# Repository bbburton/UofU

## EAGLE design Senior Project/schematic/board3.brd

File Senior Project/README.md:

# senior-project
Documentation and code for the 2022 UofU Senior Project

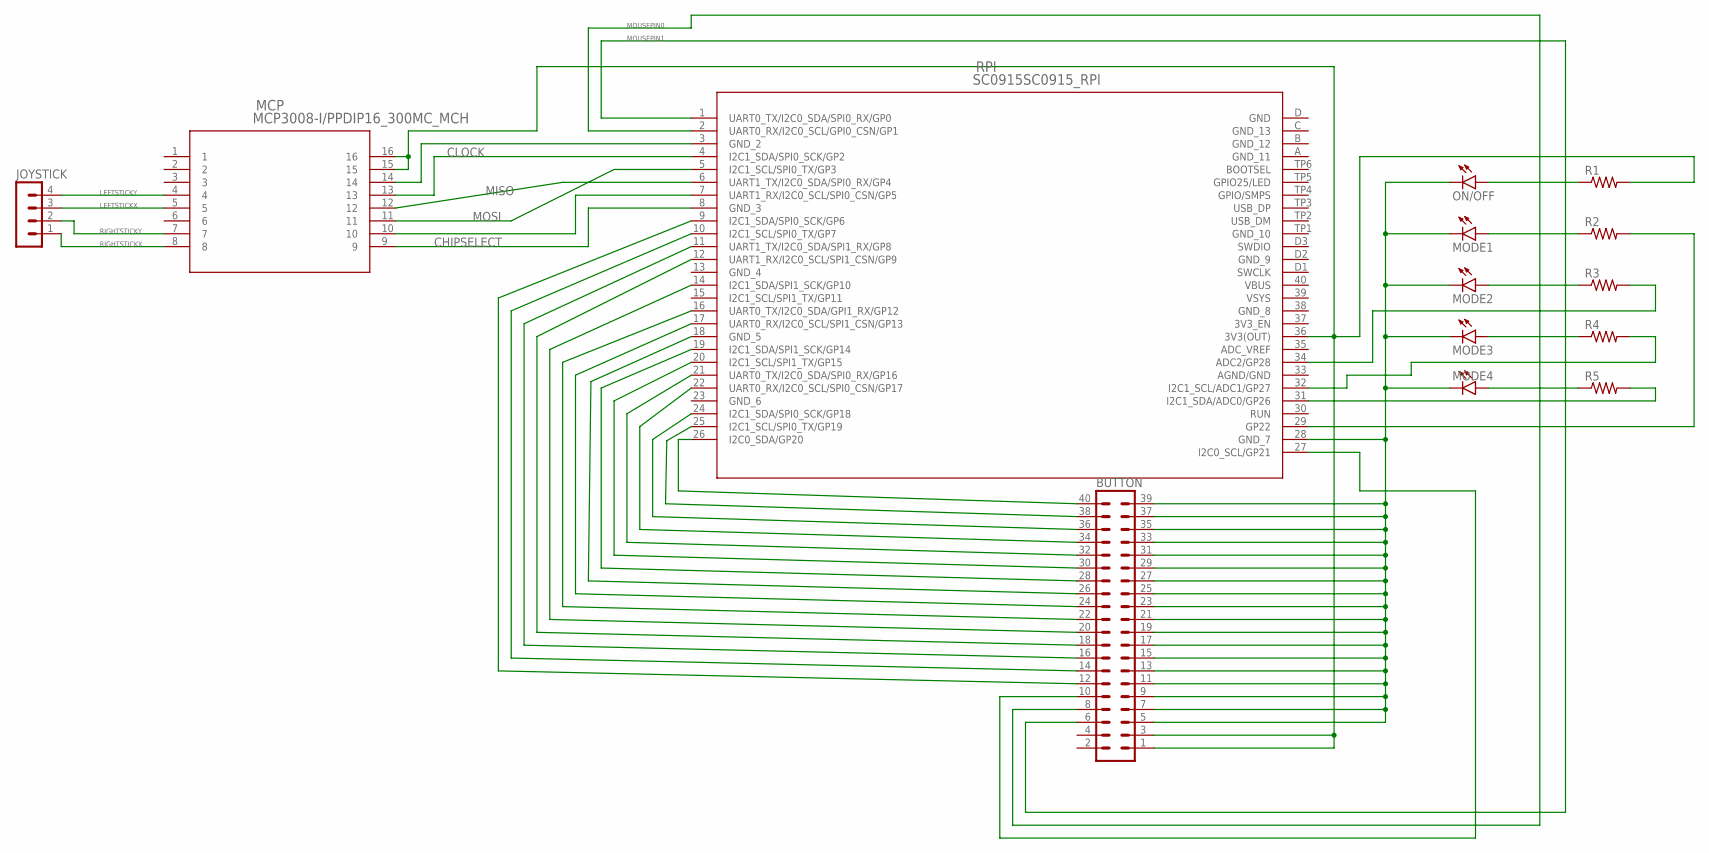
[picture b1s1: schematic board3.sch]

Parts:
BUTTON: MA20-2
JOYSTICK: MA04-1
MCP: MCP3008-I/PPDIP16_300MC_MCH; PDIP16_300MC_MCH
MODE1, MODE2, MODE3, MODE4: LED5MM
ON/OFF: LED5MM
R1, R2, R3, R4, R5: R-US_0617/17; 0617/17
RPI: SC0915SC0915_RPI; SC0915_RPI

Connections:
3V3_EN: RPI.37 (3V3_EN)
ADC_VREF: RPI.35 (ADC_VREF)
CHIPSELECT: MCP.10, RPI.7 (UART1_RX/I2C0_SCL/SPI0_CSN/GP5)
CLOCK: MCP.13, RPI.4 (I2C1_SDA/SPI0_SCK/GP2)
GND: BUTTON.5, BUTTON.7, BUTTON.9, BUTTON.11, BUTTON.13, BUTTON.15, BUTTON.17, BUTTON.19, BUTTON.21, BUTTON.23, BUTTON.25, BUTTON.27, BUTTON.29, BUTTON.31, BUTTON.33, BUTTON.35, BUTTON.37, BUTTON.39, MODE1.K (C), MODE2.K (C), MODE3.K (C), MODE4.K (C), ON/OFF.K (C), RPI.28 (GND_7)
LEFTSTICKX: JOYSTICK.3, MCP.5
LEFTSTICKY: JOYSTICK.4, MCP.4
MISO: MCP.12, RPI.6 (UART1_TX/I2C0_SDA/SPI0_RX/GP4)
MOSI: MCP.11, RPI.5 (I2C1_SCL/SPI0_TX/GP3)
MOUSEPIN0: BUTTON.8, RPI.2 (UART0_RX/I2C0_SCL/GPI0_CSN/GP1)
MOUSEPIN1: BUTTON.6, RPI.1 (UART0_TX/I2C0_SDA/SPI0_RX/GP0)
unnamed: BUTTON.36, RPI.24 (I2C1_SDA/SPI0_SCK/GP18)
unnamed: BUTTON.38, RPI.25 (I2C1_SCL/SPI0_TX/GP19)
unnamed: BUTTON.26, RPI.18 (GND_5)
unnamed: BUTTON.40, RPI.26 (I2C0_SDA/GP20)
unnamed: MCP.9, RPI.8 (GND_3)
unnamed: BUTTON.10, RPI.27 (I2C0_SCL/GP21)
unnamed: MCP.14, RPI.3 (GND_2)
unnamed: ON/OFF.A, R1.1
unnamed: BUTTON.12, RPI.9 (I2C1_SDA/SPI0_SCK/GP6)
unnamed: BUTTON.14, RPI.10 (I2C1_SCL/SPI0_TX/GP7)
unnamed: BUTTON.16, RPI.11 (UART1_TX/I2C0_SDA/SPI1_RX/GP8)
unnamed: BUTTON.18, RPI.12 (UART1_RX/I2C0_SCL/SPI1_CSN/GP9)
unnamed: BUTTON.20, RPI.14 (I2C1_SDA/SPI1_SCK/GP10)
unnamed: BUTTON.22, RPI.16 (UART0_TX/I2C0_SDA/GPI1_RX/GP12)
unnamed: BUTTON.24, RPI.17 (UART0_RX/I2C0_SCL/SPI1_CSN/GP13)
unnamed: BUTTON.28, RPI.19 (I2C1_SDA/SPI1_SCK/GP14)
unnamed: BUTTON.30, RPI.20 (I2C1_SCL/SPI1_TX/GP15)
unnamed: BUTTON.32, RPI.21 (UART0_TX/I2C0_SDA/SPI0_RX/GP16)
unnamed: BUTTON.34, RPI.22 (UART0_RX/I2C0_SCL/SPI0_CSN/GP17)
unnamed: MODE1.A, R2.1
unnamed: MODE2.A, R3.1
unnamed: MODE3.A, R4.1
unnamed: MODE4.A, R5.1
unnamed: BUTTON.1, BUTTON.3, MCP.15, MCP.16, R1.2, RPI.36 (3V3(OUT))
unnamed: R2.2, RPI.29 (GP22)
unnamed: R3.2, RPI.34 (ADC2/GP28)
unnamed: R4.2, RPI.32 (I2C1_SCL/ADC1/GP27)
unnamed: R5.2, RPI.31 (I2C1_SDA/ADC0/GP26)
RIGHTSTICKX: JOYSTICK.1, MCP.8
RIGHTSTICKY: JOYSTICK.2, MCP.7
VBUS: RPI.40 (VBUS)
VSYS: RPI.39 (VSYS)

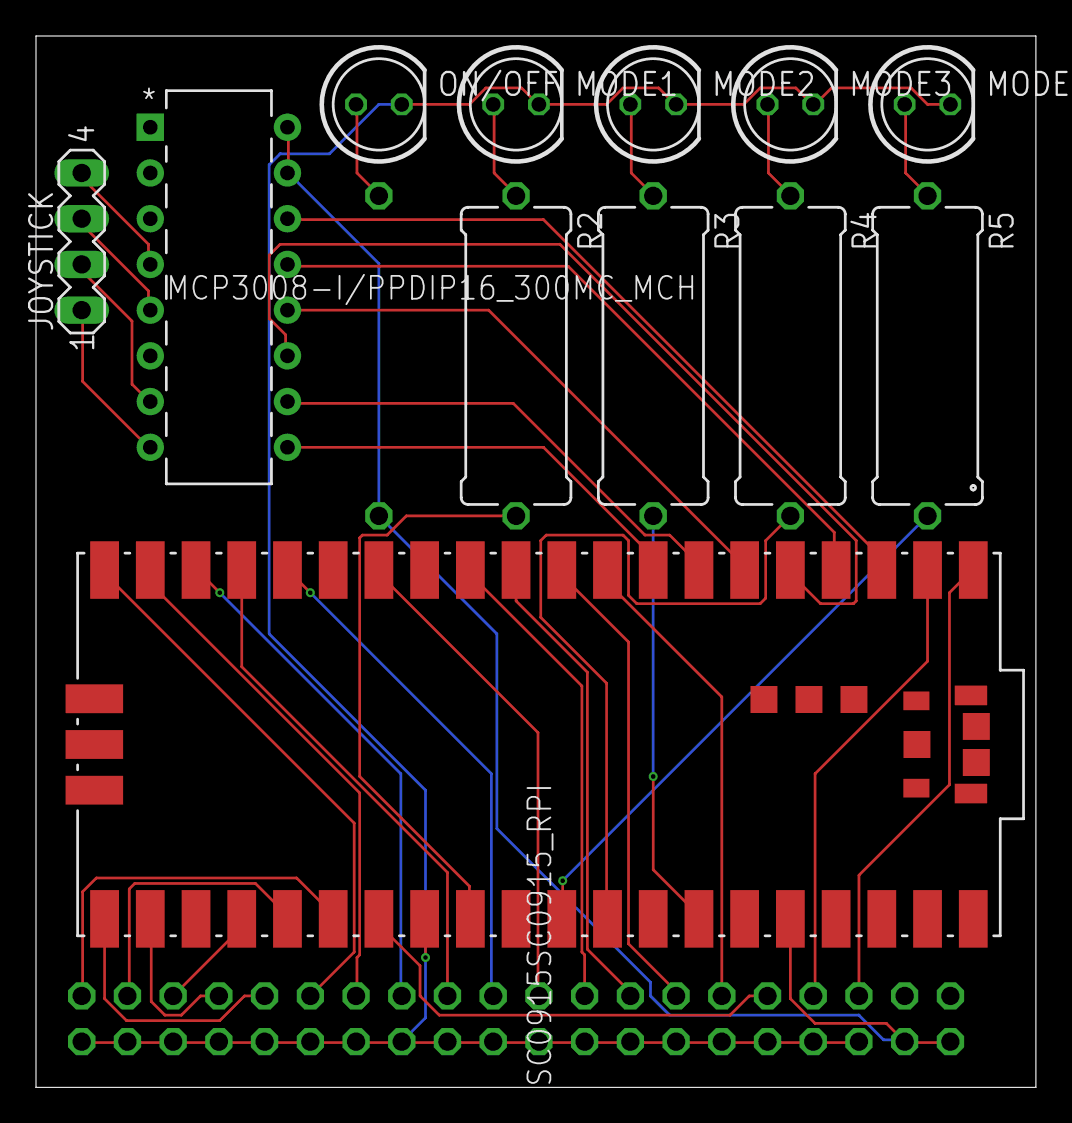
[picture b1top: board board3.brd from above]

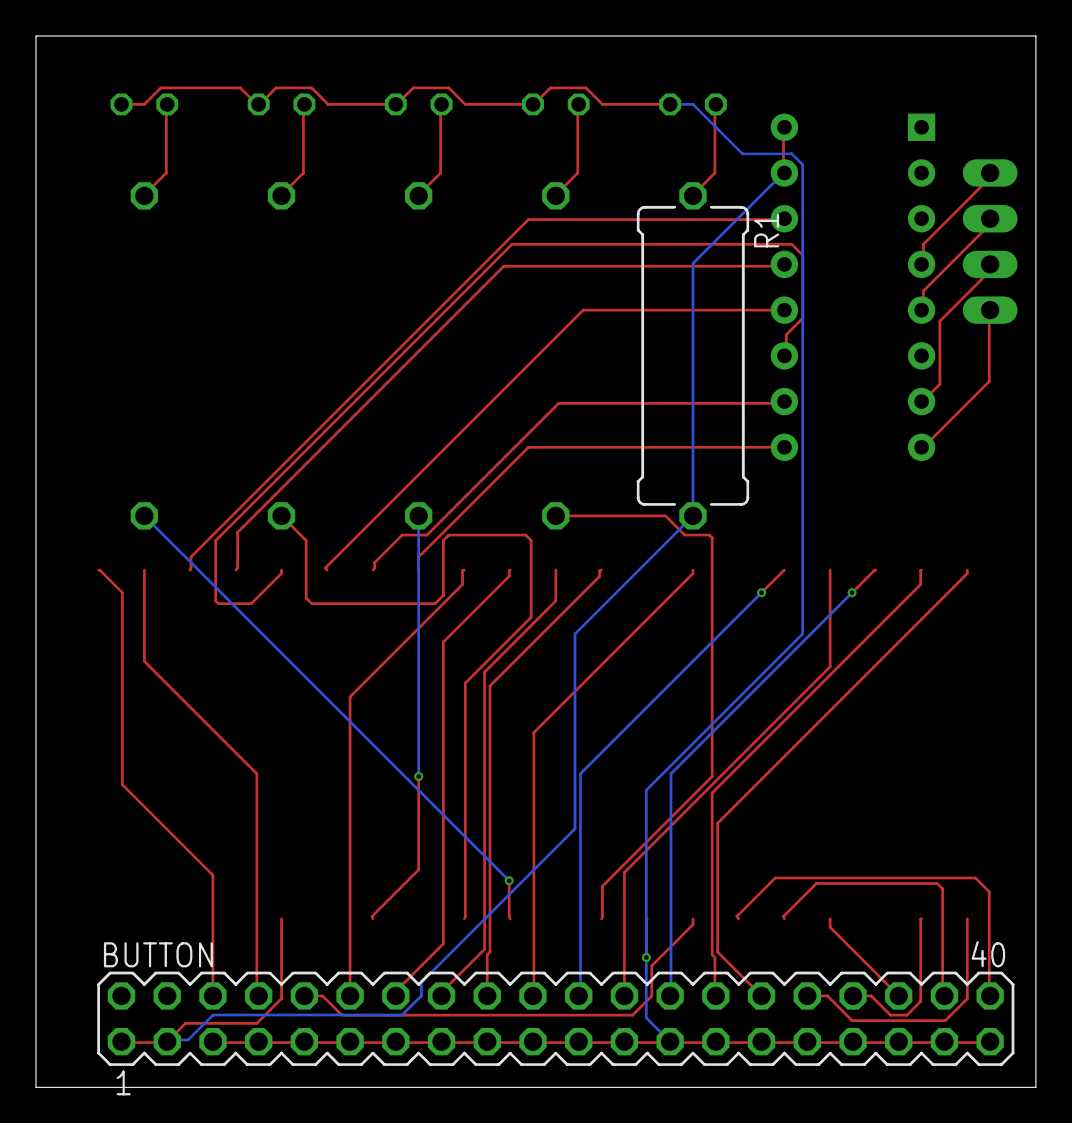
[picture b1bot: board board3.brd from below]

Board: 2 copper layers, 55.5 x 58.4 mm, 14 parts (2 on the bottom side), 39 nets.

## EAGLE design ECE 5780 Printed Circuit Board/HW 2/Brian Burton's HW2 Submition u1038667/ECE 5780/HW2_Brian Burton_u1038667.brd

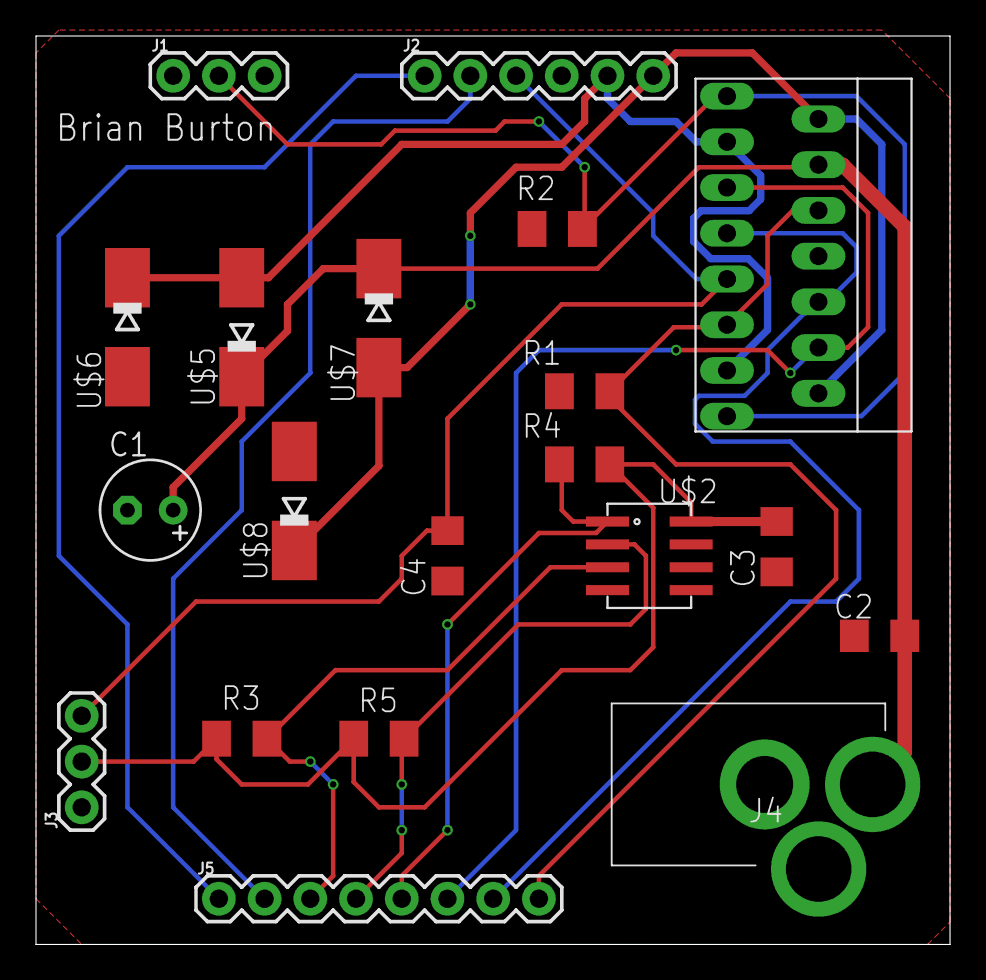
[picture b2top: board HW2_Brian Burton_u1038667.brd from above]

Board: 2 copper layers, 50.8 x 50.5 mm, 20 parts (0 on the bottom side), 15 nets.

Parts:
C1: 1uF; E2,5-6
C2, C3, C4: 100nF; C1206
J1: 1X03
J2: MTR_CTRL; 1X06
J3: MCU PWR; 1X03
J4: CON-SOCJ-2155; CONSOCJ2155
J5: 1X08
R1, R3, R4, R5: 10K; M1206
R2: 0.04; M1206
U$1: L298N-MULTIWATT15
U$2: LM75A-SOIC8; SOIC-8
U$5, U$6, U$7, U$8: SS14CT-ND; SOD106A-W

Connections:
3.3V: C3.1, J3.2, R3.2, R4.2, R5.2, U$2.8
5V: C4.1, J2.3, J3.3, U$1.9
CS: J1.2, R2.1, U$1.1, U$1.15
ENABLE: J5.8, R1.2, U$1.6, U$1.11
ENC_A: J2.2, J5.2
ENC_B: J2.1, J5.1
GND: C1.-, C2.2, C3.2, C4.2, J1.1, J1.3, J2.4, J3.1, J4.2, J4.3, R1.1, R2.2, U$1.8, U$2.4, U$2.5, U$2.6, U$2.7, U$6.A, U$8.A
IN_1: J5.7, U$1.7, U$1.10
IN_2: J5.6, U$1.5, U$1.12
MTR_BLK: J2.5, U$1.3, U$1.13, U$5.A, U$6.C
MTR_RED: J2.6, U$1.2, U$1.14, U$7.A, U$8.C
O.S.: J5.3, R3.1, U$2.3
SCL: J5.4, R5.1, U$2.2
SDA: J5.5, R4.1, U$2.1
VCC: C1.+, C2.1, J4.1, U$1.4, U$5.C, U$7.C

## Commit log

2023-01-11 Create CS 2420

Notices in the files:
parts and their libraries:
SparkFun-Connectors: Licensing: Creative Commons ShareAlike 4.0 International - https://creativecommons.org/licenses/by-sa/4.0
COPYRIGHT: Copyright (C) 2022 Ultra Librarian. All rights reserved.
